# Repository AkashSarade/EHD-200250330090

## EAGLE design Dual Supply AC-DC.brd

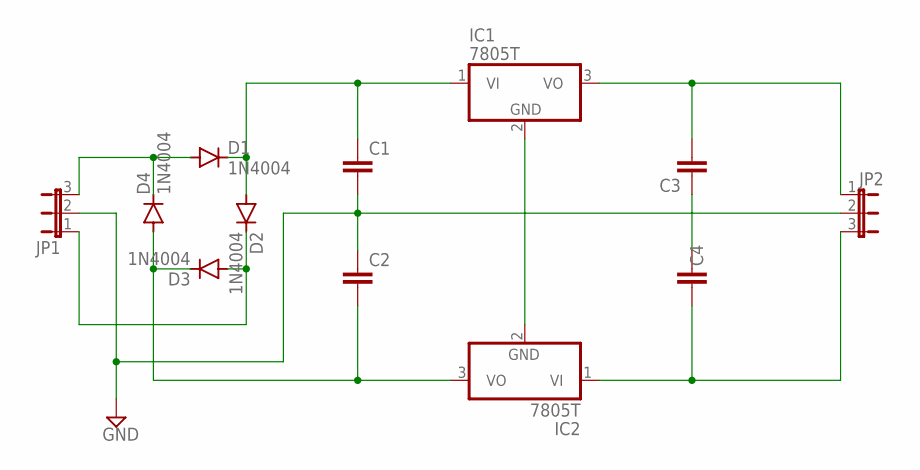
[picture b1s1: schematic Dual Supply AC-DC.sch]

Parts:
C1, C2, C3, C4: C2,5-3; C2.5-3
D1, D2, D3, D4: 1N4004; DO41-10
IC1, IC2: 7805T; TO220H
JP1, JP2: JP2E; JP2

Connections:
GND: C1.2, C2.1, JP1.2, JP2.2
unnamed: D1.A, D4.C, JP1.3
unnamed: C1.1, D1.C, D2.A, IC1.1 (VI)
unnamed: D2.C, D3.A, JP1.1
unnamed: C3.2, IC1.3 (VO), JP2.1
unnamed: IC1.2 (GND), IC2.2 (GND)
unnamed: C4.2, IC2.1 (VI), JP2.3
unnamed: C3.1, C4.1
unnamed: C2.2, D3.C, D4.A, IC2.3 (VO)

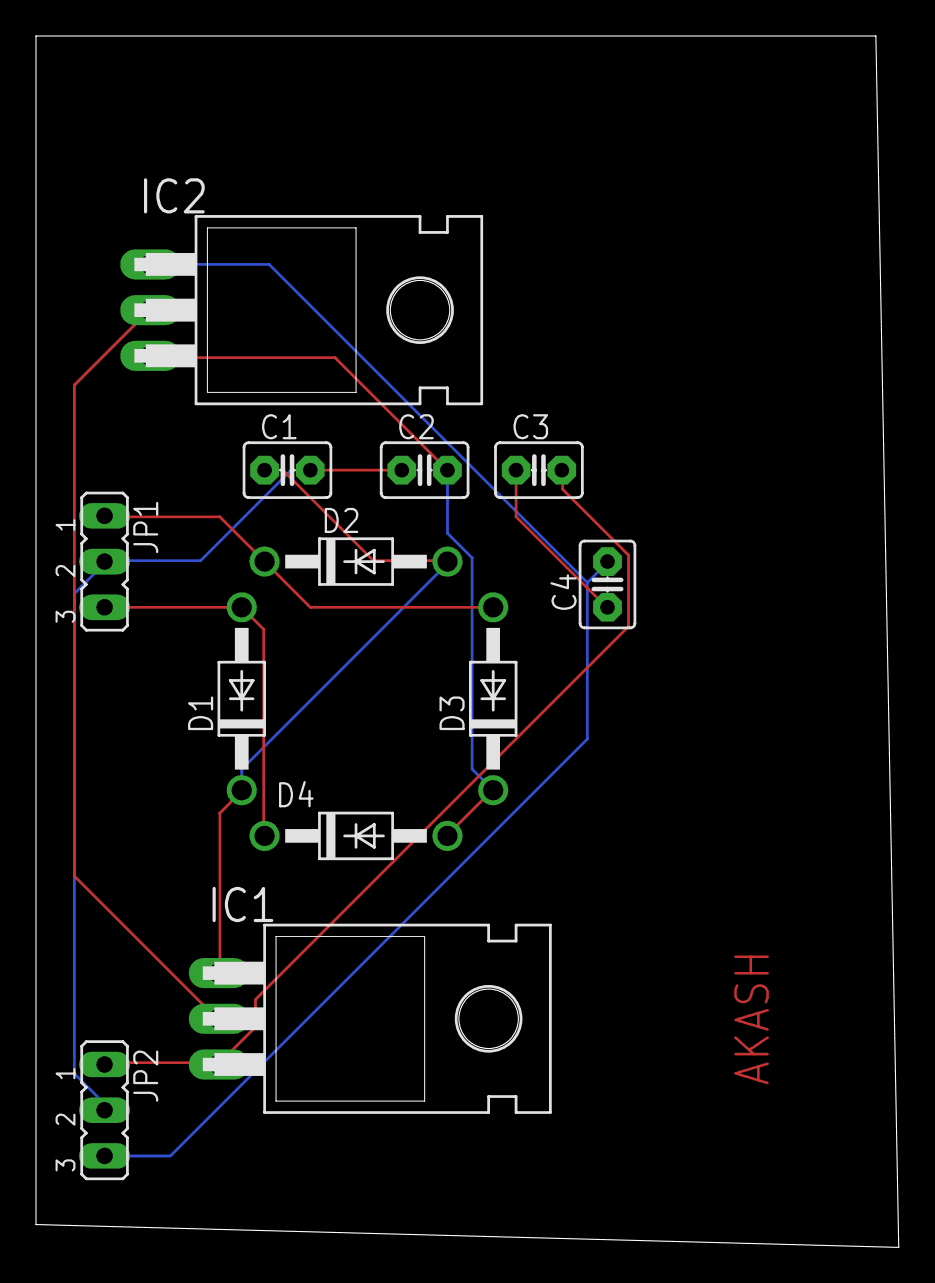
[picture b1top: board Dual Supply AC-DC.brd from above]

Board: 2 copper layers, 47.9 x 67.3 mm, 12 parts (0 on the bottom side), 9 nets.

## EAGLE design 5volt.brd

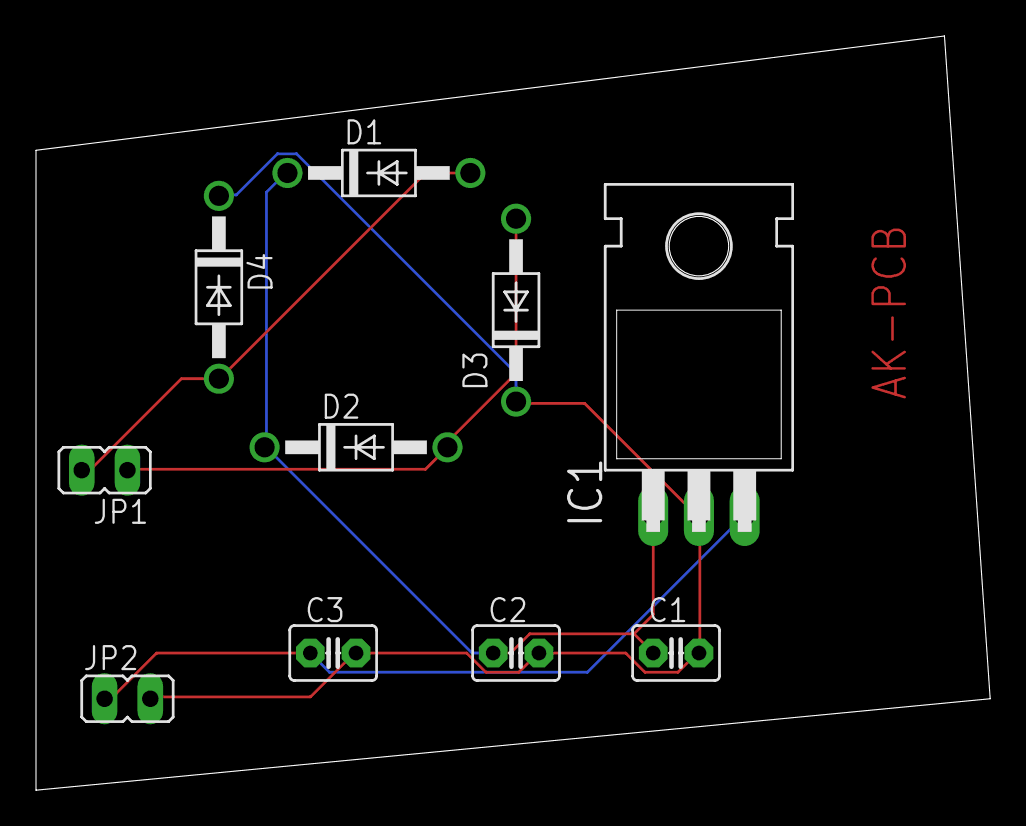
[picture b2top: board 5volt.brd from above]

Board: 2 copper layers, 53.0 x 41.9 mm, 10 parts (0 on the bottom side), 5 nets.

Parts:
C1, C2, C3: 10; C2.5-3
D1, D2, D3, D4: 1N4004; DO41-10
IC1: 7805T; TO220H
JP1: 12v; JP1
JP2: 5v; JP1

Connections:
GND: C1.2, C2.2, C3.2, D3.C, D4.C, IC1.2, JP2.2
unnamed: D1.A, D4.A, JP1.2
unnamed: C1.1, C2.1, D1.C, D2.C, IC1.1
unnamed: C3.1, IC1.3, JP2.1
unnamed: D2.A, D3.A, JP1.1
